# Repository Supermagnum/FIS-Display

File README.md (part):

# FIS-Display
VW Passat B6 FIS/MFA Display — Hardware Connections and Software Protocols.

## Table of contents

- [Disclaimer](#disclaimer)
- [What this project does](#what-this-project-does)
- [Gerber files and PCB manufacturing](#gerber-files-and-pcb-manufacturing)
- [Project structure](#project-structure)
- [1. System Overview](#1-system-overview)
- [2. Host Device — Navit with D-Bus](#2-host-device--navit-with-d-bus)
  - [2.1 Supported Platforms](#21-supported-platforms)
  - [2.2 D-Bus Service Details](#22-d-bus-service-details)
  - [2.3 Key Attributes to Subscribe To](#23-key-attributes-to-subscribe-to)
  - [2.4 Navigation Status Values](#24-navigation-status-values)
  - [2.5 D-Bus Listener to Pico Bridge Script](#25-d-bus-listener--pico-bridge-script)
- [3. Serial Protocol (Host to Pico, 115200 baud)](#3-serial-protocol-host--pico-115200-baud-newline-terminated-ascii)
  - [3.1 Eco mode icon (driver-break, D-Bus)](#31-eco-mode-icon-driver-break-d-bus)
- [4. Transport — USB CDC or Bluetooth SPP](#4-transport--usb-cdc-or-bluetooth-spp)
  - [USB CDC](#usb-cdc)
  - [Bluetooth SPP](#bluetooth-spp)
- [5. Hardware](#5-hardware)
  - [5.1 Controller — Raspberry Pi Pico 2 W](#51-controller--raspberry-pi-pico-2-w)
  - [5.2 The 3LB (Three-Line Bus)](#52-the-3lb-three-line-bus)
  - [5.3 Level Shifting](#53-level-shifting)
  - [5.4 Instrument Cluster Connector (Green T32a)](#54-instrument-cluster-connector-green-t32a)
  - [5.5 3LB connection: pigtails or wire-to-wire (Molex kit)](#55-3lb-connection-pigtails-or-wire-to-wire-molex-kit)
  - [5.6 Pico 2 W GPIO Pinout](#56-pico-2-w-gpio-pinout)
  - [5.7 Cluster Coding Prerequisite](#57-cluster-coding-prerequisite)
- [6. The 3LB Protocol](#6-the-3lb-protocol)
  - [6.1 Open Source Libraries (Reference)](#61-open-source-libraries-reference)
  - [6.2 Display](#62-display)
  - [6.3 OEM radio: CAN time and display (reference only)](#63-oem-radio-can-time-and-display-reference-only)
  - [6.4 Other potentially useful CAN messages (reference only)](#64-other-potentially-useful-can-messages-reference-only)
- [7. Firmware Runtime Behaviour](#7-firmware-runtime-behaviour)
- [8. Software Stack Summary](#8-software-stack-summary)
- [9. Key References](#9-key-references)
- [10. Possible screen upgrade](#10-possible-screen-upgrade)

---
## Disclaimer

> The creator takes no responsibility for damages, immobile car, injury, or any other loss arising from the use of this project, its firmware, PCB design, or documentation. Use at your own risk.

## What this project does

[Navit](https://github.com/navit-gps/navit) is an open-source, modular turn-by-turn navigation engine that can run on Linux, Android, and other platforms. This project uses Navit on a host device (with D-Bus enabled) to drive the car's FIS/MFA display.

This repository provides firmware, PCB design, and documentation to show Navit navigation (and optionally media, call, clock) on the VW Passat B6 (3C) FIS/MFA display. 

A host device runs Navit with D-Bus and sends a simple serial protocol to a Raspberry Pi Pico 2 W over USB or Bluetooth (pair once as FIS-Bridge). 
The Pico injects frames onto the car's 3LB bus during idle gaps so the cluster shows turn-by-turn directions, street name, distance, and maneuver icons; when not navigating, it can show media track info, incoming call caller ID, or a clock screen with GPS time, ETA (e.g. ARR 14:32), remaining distance, and compass heading. 

The firmware supports CAN bus (MCP2561 on GPIO 11/12, 100 kbit/s, software CAN 2.0A send/receive); it is disabled by default and can be enabled with CFG:CAN:1. The Pico is a middleman only; all navigation logic stays on the host. When CAN bus is enabled, it can adjust your clock automatically. 

A separate display-test firmware is provided for bench-testing the cluster without a Navit host.

PCB and schematic are designed in [KiCad](https://www.kicad.org/). Design files and Gerbers are in [pcb-files/](pcb-files/). See [Gerber files and PCB manufacturing](#gerber-files-and-pcb-manufacturing) for what they are and how to use them.

> **Note:** The firmware in `firmware/` is **experimental and untested on a real vehicle**. Validate on the bench before connecting to the car. See [firmware/README.md](firmware/README.md) for build and flash instructions; that file also explains how to install the Raspberry Pi Pico SDK if it is missing.

## Gerber files and PCB manufacturing

**What are Gerber files?** Gerber is the standard format used by PCB manufacturers to produce printed circuit boards. Each file describes one layer of the board (copper, solder mask, silkscreen, etc.) as vector graphics. The manufacturer combines these files to fabricate and assemble the PCB. This repository provides Gerbers exported from the KiCad project in [pcb-files/FIS-display/](pcb-files/FIS-display/).

**What is in this repo:** In [pcb-files/FIS-display/gerbers/](pcb-files/FIS-display/gerbers/) you will find:

- **Copper layers:** `F_Cu.gbr` (top copper), `B_Cu.gbr` (bottom copper)
- **Solder mask:** `F_Mask.gbr`, `B_Mask.gbr`
- **Silkscreen:** `F_Silkscreen.gbr`, `B_Silkscreen.gbr`
- **Solder paste (SMD stencil):** `F_Paste.gbr`, `B_Paste.gbr`
- **Board outline:** `Edge_Cuts.gbr`
- **Drill files:** `*.drl` (through-hole and non-plated drill data)

**How to use them:**

1. **Ordering PCBs:** Zip the contents of the `gerbers/` folder (all `.gbr` and `.drl` files, and the `.gbrjob` file if the manufacturer supports it) and upload the zip to a PCB fab (e.g. JLCPCB, PCBWay, OSH Park, or similar). Select the correct units (usually mm) and board thickness; the fab will use the Gerbers to produce the boards. Use the same BOM as in [firmware/BOM.md](firmware/BOM.md) for sourcing components.

2. **Viewing without KiCad:** You can inspect the layers with a Gerber viewer (e.g. [GerberView](https://www.gerber-viewer.com/), or the online viewer many fabs provide) to check traces, pads, and outline before ordering.

3. **Editing the design:** Open the KiCad project in [pcb-files/FIS-display/](pcb-files/FIS-display/) (`.kicad_pro`, `.kicad_sch`, `.kicad_pcb`) in [KiCad](https://www.kicad.org/). After any change, re-export Gerbers from KiCad (File → Plot, then generate drill files) and replace the files in `gerbers/` before ordering new boards.

---

## Project structure

This repository uses **no symlinks**; all paths are normal directories and files so that every system can clone and use it without symlink support.

| Item | Description |
|------|-------------|
| [firmware/](firmware/) | Main Pico 2 W firmware: 3LB RX/TX, serial protocol, nav/media/clock injection, graphics. |
| [firmware/README.md](firmware/README.md) | Build, flash, pinout, and firmware behaviour. |
| [firmware/BOM.md](firmware/BOM.md) | Bill of materials for the PCB. |
| [firmware-display-test/](firmware-display-test/) | Standalone display test firmware: cycles through all modes (nav text, icons, call, media, clock) every 4 seconds. |
| [firmware-display-test/README.md](firmware-display-test/README.md) | How to build and use the display test. |
| [nav-icons/](nav-icons/) | Navigation and status icon SVGs (sources for the bitmaps in `firmware/fis_nav_icons.h`). See [nav-icons/README.md](nav-icons/README.md) for adding new icons. |
| [tools/](tools/) | Build/convert helpers. [tools/svg_to_fis_icon.py](tools/svg_to_fis_icon.py) converts SVG to the 64x64 1-bit C array format. [tools/navit_dbus_to_pico_bridge.py](tools/navit_dbus_to_pico_bridge.py) runs on the host and forwards Navit D-Bus (including eco_mode_fuel_enabled) to the Pico over serial. |
| [PQ35_46_ACAN_KMatrix_V5.20.6F_20160530_MH.xlsx](PQ35_46_ACAN_KMatrix_V5.20.6F_20160530_MH.xlsx) | VW/Audi PQ35/46 CAN matrix (reference). |
| [PQ35_46_ACAN_Glossary_DE_EN.md](PQ35_46_ACAN_Glossary_DE_EN.md) | German–English translation table for the CAN matrix document. |
| [pcb-files/](pcb-files/) | PCB design (KiCad) and [Gerber files](pcb-files/FIS-display/gerbers/) for manufacturing. See [Gerber files and PCB manufacturing](#gerber-files-and-pcb-manufacturing). |

---

## 1. System Overview

```
┌──────────────────────────────────────────────────────────┐
│  Host device running Navit with D-Bus enabled            │
│                                                          │
│  Examples:                                               │
│  • Android head unit (Navit built with D-Bus support)    │
│  • Linux carputer / Raspberry Pi running Navit           │
│  • Any platform where libbinding_dbus.so is active       │
│                                                          │
│  D-Bus listener translates Navit signals to serial       │
│  protocol and forwards to Pico over USB or Bluetooth     │
└────────────┬─────────────────────────┬───────────────────┘
             │                         │
     USB CDC serial            Bluetooth SPP
     /dev/ttyACM0              (onboard CYW43439)
     (also powers Pico)        "FIS-Bridge" PIN 0000
             │                         │
             └──────────┬──────────────┘
                        │
               ┌────────▼─────────┐
               │ Raspberry Pi     │
               │ Pico 2 W         │
               │ (RP2350)         │
               │                  │
               │ Middleman:       │
               │ serial -> 3LB;   │
               │ optional: GPIO   │
               │ 11/12 -> MCP2561 │
               └────────┬─────────┘
                        │
         ┌──────────────┼──────────────┐
         │              │              │
         ▼              │              ▼
 3LB (ENA/CLK/DATA)     │      Optional CAN (if enabled):
 via BS170 level        │      GPIO 11 (TX), 12 (RX) ->
 shifters (3.3V<->5V)   │      MCP2561 (TXD/RXD) -> CAN-H/CAN-L
         │              │              │
         ▼              │              ▼
 ┌──────────────────┐   │   ┌──────────────────────────┐
 │ VW Passat B6 (3C) │   │   │ Komfort-CAN (K-CAN)      │
 │ FIS/MFA cluster   │◄──┘   │ 100 kbit/s (when fitted) │
 │ 64x88 px, 1-bit   │       └──────────────────────────┘
 └────────┬──────────┘
          │
          ▼
 ┌───────────────────────┐
 │ Original ECU          │
 │ (talks 3LB natively,  │
 │  Pico co-exists via   │
 │  ENA arbitration)     │
 └───────────────────────┘
```

The Pico 2 W is a **pure middleman**. It has no navigation intelligence — it only receives
the serial protocol from the host device and injects the translated frames onto the 3LB bus.

All navigation logic stays on the host device running Navit. Optionally, when CAN is enabled
(see [5.6 Pico 2 W GPIO Pinout](#56-pico-2-w-gpio-pinout)), the Pico can communicate with the
vehicle Komfort-CAN (Comfort CAN / K-CAN, 100 kbit/s) via GPIO 11/12 to the MCP2561 (TXD/RXD only).

The original ECU continues to talk to the FIS/MFA natively over 3LB at all times. The Pico co-exists on the bus using the ENA line for arbitration — no relay or analog switch is needed.

> **Note:** The OEM radio has been replaced with an aftermarket head unit. The head unit does
> **not** communicate over 3LB. Only the original ECU talks to the FIS/MFA natively over 3LB.

---

## 2. Host Device — Navit with D-Bus

### 2.1 Supported Platforms

Navit can be built with D-Bus support (`libbinding_dbus.so`) on multiple platforms:

| Platform | Notes |
|----------|-------|
| Android head unit | Navit built with D-Bus support. Android includes D-Bus (`android_external_dbus`) |
| Linux carputer | Native D-Bus session bus, full support |
| Raspberry Pi (Linux) | Native D-Bus session bus, full support |
| Any Linux-based system | Native D-Bus session bus, full support |

Enable D-Bus in `navit.xml`:
```xml
<plugin path="$NAVIT_LIBDIR/*/${NAVIT_LIBPREFIX}libbinding_dbus.so" active="yes"/>
```

### 2.2 D-Bus Service Details

| Item | Value |
|------|-------|
| Service name | `org.navit_project.navit` |
| Bus type | Session bus |
| Main object | `/org/navit_project/navit/default_navit` |
| Route object | `/org/navit_project/navit/default_navit/default_route` |
| Vehicle object | `/org/navit_project/navit/default_navit/default_vehicle` |

### 2.3 Key Attributes to Subscribe To

| Attribute | Meaning |
|-----------|---------|
| `navigation_next_turn` | Upcoming maneuver type |
| `navigation_distance_turn` | Metres to next turn |
| `navigation_street_name` | Next street name |
| `navigation_street_name_systematic` | Route number |
| `navigation_status` | Routing state |
| `position_speed` | Current speed |
| `eta` | Estimated arrival (Unix timestamp); sent as `NAV:ETA`, shown in local time on FIS clock line |
| `destination_length` | Remaining distance to destination (m); sent as `NAV:REMAIN`, shown on FIS clock line |
| `position_direction` | Heading in degrees (0-360); sent as `NAV:HEAD`, shown as compass (N, NE, E, ...) on FIS |
| `position_time_iso8601` | GPS time UTC, format `YYYY-MM-DDTHH:MM:SSZ` (for FIS clock) |
| `position_coord_geo` | GPS latitude/longitude (for timezone lookup; vehicle attribute) |

### 2.4 Navigation Status Values

| Value | Meaning |
|-------|---------|
| `no_route` | No active route |
| `no_destination` | No destination set |
| `position_wait` | Waiting for GPS |
| `calculating` | Initial calculation |
| `recalculating` | Rerouting |
| `routing` | Active guidance |

### 2.5 D-Bus Listener to Pico Bridge Script

A bridge script runs on the host device and forwards Navit D-Bus attributes to the Pico over USB CDC or Bluetooth SPP. This repo includes **`tools/navit_dbus_to_pico_bridge.py`**, which implements the protocol and **eco_mode_fuel_enabled** support (Driver Break plugin): when `get_attr("eco_mode_fuel_enabled")` is true and a route has just been calculated (`navigation_status` = `routing`), it sends the eco icon for a short period (default 2.5 s), then the real first turn and distance so the FIS never shows eco instead of routing.

The driver-break plugin is awaiting merge and hardware testing; see [navit-gps/navit#1419](https://github.com/navit-gps/navit/pull/1419).

**Run (host):**
```bash
python3 tools/navit_dbus_to_pico_bridge.py --port /dev/ttyACM0   # USB CDC
python3 tools/navit_dbus_to_pico_bridge.py --port /dev/rfcomm0 --eco-seconds 2.5   # Bluetooth SPP
```

**Requirements:** Python 3, `pyserial`, PyGObject (`gi.repository.GLib`), `dbus`. Optional: Driver Break plugin in Navit for `eco_mode_fuel_enabled` (OBD-II / J1939 / MegaSquirt or adaptive fuel learning).

**Inline example (minimal, no eco logic)** for reference:

```python
#!/usr/bin/env python3
"""
Navit D-Bus listener -> Pico 2 W serial bridge.
Runs on any platform where Navit is built with libbinding_dbus.so active:
Android (with D-Bus support), Linux carputer, Raspberry Pi, etc.
Transport: USB CDC or Bluetooth SPP -- configure SERIAL_PORT below.
"""

import serial
import dbus
import dbus.mainloop.glib
from gi.repository import GLib

SERIAL_PORT = "/dev/ttyACM0"   # USB CDC, or e.g. /dev/rfcomm0 for Bluetooth SPP
BAUD = 115200

WATCHED = [
    "navigation_next_turn",
    "navigation_distance_turn",
    "navigation_street_name",
    "navigation_status",
    "eta",
    "destination_length",      # remaining distance (m) -> NAV:REMAIN, shown on FIS clock line
    "position_direction",      # heading 0-360 -> NAV:HEAD, shown as compass (N, NE, E, ...)
    "position_time_iso8601",   # UTC GPS time for FIS clock (format YYYY-MM-DDTHH:MM:SSZ)
    "position_coord_geo",      # lat/lon for timezone lookup (vehicle attribute)
]

MANEUVER_MAP = {
    "straight":          "straight",
    "turn_left":         "turn_left",
    "turn_right":        "turn_right",
    "turn_slight_left":  "slight_left",
    "turn_slight_right": "slight_right",
    "turn_sharp_left":   "sharp_left",
    "turn_sharp_right":  "sharp_right",
    "u_turn":            "u_turn",
    "keep_left":         "keep_left",
    "keep_right":        "keep_right",
    "destination":       "destination",
}

class NavitBridge:
    def __init__(self):
        self.ser = serial.Serial(SERIAL_PORT, BAUD, timeout=1)
        dbus.mainloop.glib.DBusGMainLoop(set_as_default=True)
        bus = dbus.SessionBus()
        obj = bus.get_object("org.navit_project.navit",
                             "/org/navit_project/navit/default_navit")
        iface = dbus.Interface(obj, dbus_interface="org.navit_project.navit")
        cb_path = iface.callback_attr_new()
        for attr in WATCHED:
            iface.add_attr(cb_path, attr)
        bus.add_signal_receiver(
            self.on_update,
            signal_name="callback_attr_update",
            dbus_interface="org.navit_project.navit",
            path=cb_path,
        )

    def on_update(self, attr_name, value):
        msg = None
        if attr_name == "navigation_next_turn":
            code = MANEUVER_MAP.get(str(value), str(value))
            msg = f"NAV:TURN:{code}\n"
        elif attr_name == "navigation_distance_turn":
            msg = f"NAV:DIST:{int(value)}\n"
        elif attr_name == "navigation_street_name":
            msg = f"NAV:STREET:{str(value)[:20]}\n"
        elif attr_name == "navigation_status":
            msg = f"NAV:STATUS:{str(value)}\n"
        elif attr_name == "eta":
            msg = f"NAV:ETA:{int(value)}\n"
        elif attr_name == "destination_length":
            msg = f"NAV:REMAIN:{int(value)}\n"
        elif attr_name == "position_direction":
            msg = f"NAV:HEAD:{int(value)}\n"
        elif attr_name == "position_time_iso8601":
            msg = f"NAV:TIME:{str(value)}\n"
        elif attr_name == "position_coord_geo":
            # value is typically (lng, lat) or struct; adapt to your D-Bus binding
            try:
                lat, lon = float(value[1]), float(value[0])  # (lng, lat) from Navit
                msg = f"NAV:POS:{lat:.4f},{lon:.4f}\n"
            except (IndexError, TypeError, ValueError):
                pass
        if msg:
            self.ser.write(msg.encode())

    def run(self):
        GLib.MainLoop().run()

if __name__ == "__main__":
    NavitBridge().run()
```

For full behaviour including eco icon when `eco_mode_fuel_enabled` is true, use **`tools/navit_dbus_to_pico_bridge.py`** (see above).

---

## 3. Serial Protocol (Host → Pico, 115200 baud, newline-terminated ASCII)

The same protocol is used regardless of whether the transport is USB CDC or Bluetooth SPP.

| Message | Meaning |
|---------|---------|
| `NAV:TURN:<code>` | Upcoming maneuver type. For eco icon (driver-break) see [3.1 Eco mode icon](#31-eco-mode-icon-driver-break-d-bus): use `eco_mode` or `eco` only when `eco_mode_fuel_enabled` is true and route is ready (see 3.1); it must **not** override routing instructions. |
| `NAV:DIST:<metres>` | Distance to next turn |
| `NAV:STREET:<n>` | Next street name (max 20 chars) |
| `NAV:STATUS:<status>` | Navit routing status |
| `NAV:ETA:<unix_ts>` | Estimated arrival (Unix timestamp); converted to local time and shown on clock line 2 as e.g. ARR14:32 |
| `NAV:REMAIN:<metres>` | Remaining distance to destination (from Navit `destination_length`); shown on clock line |
| `NAV:HEAD:<degrees>` | Heading 0-360 (from Navit `position_direction`); shown as compass on clock line |
| `NAV:TIME:<iso8601>` | GPS time UTC, e.g. `2026-03-14T12:34:56Z` (from Navit `position_time_iso8601`) |
| `NAV:POS:<lat>,<lon>` | GPS position in decimal degrees (from Navit `position_coord_geo`), e.g. `59.91,10.75` |
| `BT:TRACK:<info>` | Media track info from head unit |
| `BT:CALL:<caller>` | Incoming call caller ID |
| `BT:CALLEND` | Call ended |

### 3.1 Eco mode icon (driver-break, D-Bus)

The **eco mode** icon on the FIS is intended for the [Driver Break plugin](https://github.com/Supermagnum/navit/blob/feature/driver-break/docs/user/plugins/driver-break/index.rst) when fuel/energy is used in routing (ECU or adaptive fuel data). It must **never override routing instructions**: the host must only show the eco icon when appropriate and only for a short moment (e.g. after route planning finishes, before the first maneuver is displayed).

**Driver-break D-Bus attribute: `eco_mode_fuel_enabled`**

The plugin exposes a boolean attribute **eco_mode_fuel_enabled** on the Navit D-Bus interface. It is **true** when either (1) an ECU backend is available and running (OBD-II, J1939, or MegaSquirt), or (2) adaptive fuel learning is enabled in the plugin configuration. When **false**, no live ECU data and no adaptive learning are in use (energy-based routing may still be available without fuel data). See the [Driver Break D-Bus API (eco_mode_fuel_enabled)](https://github.com/Supermagnum/navit/blob/feature/driver-break/docs/user/plugins/driver-break/dbus.rst) for service, object path, interface, and examples in Python and `dbus-send`.

- **Service:** `org.navit_project.navit`
- **Method:** `get_attr("eco_mode_fuel_enabled")` on the navit object; returns `(attrname, value)` with a D-Bus boolean.

**When to show the eco icon**

- **`eco_mode_fuel_enabled` is true** (ECU running or adaptive fuel learning enabled).
- **Navit has planned or finished planning** a route that uses energy-based routing (fuel cost in the cost function).
- **Do not show eco when there is an active maneuver to display.** Example flow: when Navit finishes calculating a route and the above conditions are true, show the eco icon for a short period (e.g. 2–3 seconds), then send the actual first turn (`navigation_next_turn`) and distance so the FIS switches to normal turn-by-turn. The eco icon is an informational "route was planned with eco/fuel" hint, not a substitute for maneuver icons.

**Bridge script logic**

1. **Read the attribute** (e.g. on a timer or when `navigation_status` changes): call `get_attr("eco_mode_fuel_enabled")` on the navit object (see [dbus.rst](https://github.com/Supermagnum/navit/blob/feature/driver-break/docs/user/plugins/driver-break/dbus.rst) for object path and Python/dbus-send examples).
2. **Policy:** Send `NAV:TURN:eco_mode` to the Pico only when:
   - `eco_mode_fuel_enabled` is true, and
   - Route planning has just completed (e.g. `navigation_status` went to `routing`) or the route is ready and you are about to send the first maneuver.
3. Send `NAV:TURN:eco_mode` for a **short fixed duration** (e.g. 2–3 seconds), then immediately send the real first turn and distance (`NAV:TURN:<code>`, `NAV:DIST:<m>`) so the FIS shows the actual routing instruction. Never send or keep sending `eco_mode` when the user should see a turn icon (left, right, etc.).

The driver-break plugin is awaiting merge into the official Navit repo and hardware testing. See: https://github.com/navit-gps/navit/pull/1419

**Firmware behaviour:** The Pico displays whatever `NAV:TURN` code the host last sent. The **host is responsible** for never letting eco_mode override a maneuver: the bridge must only send `NAV:TURN:eco_mode` in the narrow window described above and then replace it with the real maneuver.

**Summary:** Eco icon = show only when `eco_mode_fuel_enabled` is true and route planning has just finished; display it briefly, then always switch to the real first (and subsequent) routing instructions.

**Feature toggles (clock screen):** Send `CFG:<name>:0` or `CFG:<name>:1` to enable or disable what is shown. Clock/ETA/compass/remain default to 1 (on). CAN bus has **full firmware support** (send/receive, 100 kbit/s, MCP2561) but is **disabled by default** (0).

| Message | Effect |
|---------|--------|
| `CFG:CLOCK:0` / `CFG:CLOCK:1` | Clock (time from GPS, set automatically); 0 = do not show clock on FIS |
| `CFG:ETA:0` / `CFG:ETA:1` | ETA in local time on clock line 2 (e.g. ARR14:32) |
| `CFG:COMPASS:0` / `CFG:COMPASS:1` | Compass heading (N, NE, ...) on clock line 2 |
| `CFG:REMAIN:0` / `CFG:REMAIN:1` | Remaining distance on clock line 2 |
| `CFG:CAN:0` / `CFG:CAN:1` | CAN bus (full support: send/receive at 100 kbit/s, **disabled by default**). Enable with 1 when MCP2561 is connected to GPIO 11/12. |

---

## 4. Transport — USB CDC or Bluetooth SPP

The host device can connect to the Pico over either transport. The Pico listens on both
USB CDC and Bluetooth SPP simultaneously.

### USB CDC
- Connect a USB cable from the host to the Pico USB port
- Pico appears as `/dev/ttyACM0` (Linux) or equivalent on Android
- **Also provides 5 V power to the Pico via VSYS** — no separate power supply needed
- Baud rate: 115200

### Bluetooth SPP
- Pico advertises as `FIS-Bridge` using classic Bluetooth SPP via BTstack (onboard CYW43439)
- No external Bluetooth module required
- **Pair once:** scan for `FIS-Bridge`, enter PIN `0000` if prompted — reconnects automatically
- On Linux: Pico appears as `/dev/rfcomm0` after pairing
- Baud rate: 115200

> If using Bluetooth only (no USB), the Pico needs a separate 5 V power source via the VSYS
> pin — e.g. a car USB adapter or a 12 V → 5 V regulator on the PCB.

---

## 5. Hardware

### 5.1 Controller — Raspberry Pi Pico 2 W

| Property | Value |
|----------|-------|
| MCU | RP2350 (dual-core Cortex-M33, 150 MHz) |
| RAM | 520 KB SRAM |
| Flash | 4 MB |
| Wireless | Infineon CYW43439 — WiFi + classic Bluetooth |
| Logic level | 3.3 V GPIO |
| Power | 5 V via VSYS (USB or external) |
| DigiKey P/N | SC0919 |

### 5.2 The 3LB (Three-Line Bus)

| Wire | Function | Direction |
|------|----------|-----------|
| ENA | Enable / bus arbitration | Bidirectional |
| DATA | Serial data | Master → Cluster |
| CLK | Clock | Master → Cluster |

Bus runs at **5 V logic**. The 3LB clock speed is **suspected to be ~125–130 kHz** (transmission/bit rate). The actual documented value is difficult to find; the BAP FCNav function catalogue does not specify the physical layer, and other sources sometimes quote conflicting numbers (e.g. 2300 Hz or 2300 kHz). The firmware is configured for ~125 kHz by default; see below for how to measure the speed on your bus and adjust the code. Pico GPIO is 3.3 V — level shifting required on all lines.

**Bus arbitration:** Before transmitting, a master pulls ENA low to claim the bus. If ENA is already
low (another device is transmitting), it waits. The cluster acknowledges with a 100 µs pulse (e.g. ENA high). The Pico and ECU safely share the bus without any relay or switch.

**Measuring 3LB clock speed and adjusting the firmware:** To confirm or correct the bus speed on your cluster:

1. **Measure the CLK line** with an oscilloscope or logic analyzer while the OEM radio or nav unit is transmitting to the cluster (or while the Pico is transmitting). Measure the frequency of the CLK signal during an active frame (ENA low). One full clock period = one bit; the frequency in Hz is the bit rate.
2. **If your measured frequency differs from ~125 kHz**, edit the firmware to match. In `firmware/fis_display.c`, change the constant `FIS_3LB_TX_CLK_HZ` (default 125000) to your measured value in Hz. Rebuild and flash. Example: if you measure 130 kHz, set `#define FIS_3LB_TX_CLK_HZ 130000u`.
3. **Optional:** If you have a different PIO program with a different number of cycles per bit, adjust `FIS_3LB_TX_CYCLES_PER_BIT` (default 6) to match so the divider calculation stays correct.

### 5.3 Level Shifting

6× **BS170** N-channel MOSFET (TO-92, through-hole), one per 3LB GPIO line (3 RX + 3 TX).
Each channel uses two 2.2 kΩ pull-up resistors — one to 3.3 V, one to 5 V. Use non-inductive resistors (e.g. metal film or SMD thick/thin film); avoid wirewound types.

| Part | DigiKey P/N | Qty |
|------|-------------|-----|
| BS170 MOSFET TO-92 THT | BS170-ND | 6 |
| 2.2 kΩ resistor 0.25 W THT (non-inductive) | — | 12 |

BS170 pinout (flat face toward you, left to right): **Source — Gate — Drain**.

### 5.4 Instrument Cluster Connector (Green T32a)

| T32a Pin | Signal |
|----------|--------|
| 30 | DATA |
| 31 | CLK |
| 32 | ENA |

Connector type: Kostal MLK 1.2 / MQS 0.63 mm. Use a VAG pin tool to back-probe terminals.
Do not cut harness wires unless you are absolutely sure what you are doing.
One option is to cut the harness wires needed and add connectors so you can plug the PCB in line; then you can unplug both sides and connect them directly to bypass the board for repairs or to restore original function. Use the Molex 3-circuit kit (see below) for pigtails from the PCB or for a pure wire-to-wire connection.

### 5.5 3LB connection: pigtails or wire-to-wire (Molex kit)

No PCB-mounted connector. Use one **Molex 3-circuit connector kit** (DigiKey **23-0766500064-ND**, Molex **0766500064**, "KIT CONN STD .062" 3 CIRCUITS"). The kit is the complete solution for both PCB pigtails and wire-to-wire.

**With PCB (pigtails):** Solder two short pigtail wires directly to the PCB RX and TX pad areas. On the free end of each pigtail, crimp the correct connector from the kit:

| Side | PCB pad | Free end (from kit) |
|------|---------|---------------------|
| **RX** | Solder wire to PCB RX pads | Female receptacle housing **0003061038** with socket terminals **0002061103** |
| **TX** | Solder wire to PCB TX pads | Plug housing **0003062033** with pin terminals **0002062103** |

Incoming field cables then plug into those pigtails — female into male, male into female. The different housing genders prevent swapping RX and TX.

**Wire-to-wire (no PCB):** To connect two cables with no board in between, plug the kit female receptacle housing directly into the male plug housing. No PCB, no soldering, no extra parts.

| Part | DigiKey P/N | Qty |
|------|-------------|-----|
| Molex 3-circuit connector kit (.062" / 1.57 mm) | 23-0766500064-ND | 1 |

### 5.6 Pico 2 W GPIO Pinout

**3LB RX — monitor ECU frames, detect bus idle (inputs, via level shifter):**

| GPIO | Signal |
|------|--------|
| GPIO0 | FIS_PIN_ENA — monitors bus idle state |
| GPIO1 | FIS_PIN_CLK — input to PIO SM0 |
| GPIO2 | FIS_PIN_DATA — input to PIO SM0 |

**3LB TX — inject frames during idle gaps (outputs, via level shifter):**

| GPIO | Signal |
|------|--------|
| GPIO3 | FIS_PIN_ENA_OUT — claims bus before injecting |
| GPIO4 | FIS_PIN_CLK_OUT — PIO SM1 side-set |
| GPIO5 | FIS_PIN_DATA_OUT — PIO SM1 out_base |

**Optional CAN (firmware supports full CAN; when enabled, MCP2561):** On the VW Passat B6 (PQ46 platform) the bus connecting the instrument cluster to the rest of the modules is the **Komfort-CAN** (Comfort CAN), also referred to as **K-CAN** or **KCAN**. The CAN transceiver used is the MCP2561. It has only 2 signal connections: TXD and RXD. 3.3 V logic; no level shifter needed. See `firmware/fis_can.h` and firmware README.

| GPIO   | Signal         | Direction | Notes                    |
|--------|----------------|-----------|---------------------------|
| GPIO11 | FIS_CAN_PIN_TX | Out       | TX CAN to MCP2561 TXD     |
| GPIO12 | FIS_CAN_PIN_RX | In        | RX CAN from MCP2561 RXD   |

MCP2561 CANH/CANL connect to the vehicle Komfort-CAN (Comfort CAN / K-CAN, 100 kbit/s). For when to add a 120 ohm termination (tapped in middle vs replacing radio vs bench), see firmware README.

**PQ46 CAN buses:** The Komfort-CAN is distinct from the other two CAN buses on the platform:

| Bus | Bit rate | Typical traffic |
|-----|----------|------------------|
| **Komfort-CAN** (K-CAN) | 100 kbit/s | Instrument cluster, convenience modules, gateway; messages like mKombi_1, mDiagnose_1 |
| **Antriebs-CAN** (ACAN / Drivetrain CAN) | 500 kbit/s | Engine, ABS, airbag, gearbox |
| **Infotainment-CAN** (ICAN) | 100 kbit/s | Radio, navigation, phone module |

The **CAN gateway (J533)** sits between these buses and bridges messages as needed. When your Pico (via MCP2561) taps into the bus to read or send messages such as mKombi_1, mDiagnose_1, etc., it is connecting to the **Komfort-CAN** (K-CAN), not to ACAN or ICAN.

### 5.7 Cluster Coding Prerequisite

Code the cluster using **VCDS** or **OBDeleven**, Module **17 — Instruments**:
enable **"Navigation present"**. Without this the navigation slot in the FIS/MFA is inactive
even if the Pico sends correct 3LB frames.

---

## 6. The 3LB Protocol

### 6.1 Open Source Libraries (Reference)

| Library | URL | Notes |
|---------|-----|-------|
| TLBFISLib | https://github.com/domnulvlad/TLBFISLib | Most complete, actively maintained |
| VAGFISWriter | https://github.com/tomaskovacik/VAGFISWriter | Original reverse-engineered implementation |
| FISCuntrol | https://github.com/adamforbes92/FISCuntrol | Complete project, author uses in own car |
| FISBlocks | https://github.com/ibanezgomez/FISBlocks | 3LB + KWP1281 OBD combined |

The Pico firmware reimplements 3LB directly in PIO state machines timed to the BAP FCNav
SDP30DF48V280F specification — no Arduino library dependency.

### 6.2 Display

The FIS/MFA (Fahrerinformationssystem / Multifunktionsanzeige) screen is a **64×88 pixel
monochrome LCD**, 1-bit. Navigation maneuver icons are pre-generated 64×64 px 1-bit arrays
stored in flash (`firmware/fis_nav_icons.h`) and rendered with:
```c
GraphicFromArray(x, y, width, height, array, 0); // 0 = flash/PROGMEM
```

### 6.3 OEM radio: CAN time and display (reference only)

The **original VW radio** set the instrument cluster time via the **CAN bus** (CAN-H / CAN-L), using time it received from the **FM RDS network**. This project does **not** use CAN for the clock; the Pico sets the FIS clock from GPS (Navit) over serial and 3LB only. The following is documented for reference.

**OEM messages implemented:** When CAN is enabled (`CFG:CAN:1`), the firmware sends **mDiagnose_1** (0x7D0) with local date/time derived from GPS (NAV:TIME + position for timezone) every 1000 ms, and **mEinheiten** (0x60E) with display format (24 h, EU date, units). The cluster can use mDiagnose_1 to set its internal clock. The FIS clock display is still driven by the serial protocol and 3LB injection; mDiagnose_1 allows the cluster’s own time display to stay in sync when CAN is connected.

| Message | CAN ID | Length | Period | Description |
|---------|--------|--------|--------|-------------|
| **mDiagnose_1** | 0x7D0 (2000) | 8 bytes | 1000 ms | Date and time from radio (e.g. RDS). |
| **mEinheiten** | 0x60E (1550) | 2 bytes | 1000 ms | Display format flags (date/clock on-off, day of week). |

**mDiagnose_1 (0x7D0) — date and time**

| Signal | Byte | Start bit | Length | Range | Unit |
|--------|------|------------|--------|-------|------|
| DI1_Jahr (Year) | 4 | 4 | 7 bits | 0–127 → 2000–2127 | Year |
| DI1_Monat (Month) | 5 | 3 | 4 bits | 1–12 | Month |
| DI1_Tag (Day) | 5 | 7 | 5 bits | 0–31 | Day |
| DI1_Stunde (Hour) | 6 | 4 | 5 bits | 0–23 | Hours |
| DI1_Minute (Minute) | 7 | 1 | 6 bits | 0–59 | Minutes |
| DI1_Sekunde (Second) | 7 | 7 | 6 bits | 0–59 | Seconds |
| DI1_Zeit_alt (time stale) | 8 | 7 | 1 bit | — | 1 = time old/stale |

Sent cyclically every 1000 ms.

**mEinheiten (0x60E) — display format**

| Signal | Byte | Bit(s) | Description |
|--------|------|--------|-------------|
| EH1_Datum_Anzeige | 1 | 6 | Date display on/off |
| EH1_Uhr_Anzeige | 1 | 7 | Clock display on/off |
| EH1_Wochentag | 2 | 4–6 | Day of week |

Sent cyclically every 1000 ms.

### 6.4 Other potentially useful CAN messages (reference only)

**mDiagnose_1** and **mEinheiten** are implemented and sent when CAN is enabled (see 6.3). The following CAN frames are not yet implemented; they are documented for reference. You can add handling for these or other IDs using `fis_can_send()` / `fis_can_receive()`.

**Useful for FIS/display**

- **mKombi_1 (0x320)** — sent by the cluster, 10 ms cyclic: KO1_kmh (vehicle speed, bytes 4–5, 15 bits), KO1_angez_kmh (displayed speed including offset, bytes 6–7), KO1_Tankinhalt (fuel level), KO1_Warn_Tank (low fuel, 7 L), KO1_Oeldruck (oil pressure warning), KO1_Kuehlmittel (coolant warning), KO1_Vorgluehen (glow plug, diesel).
- **mKombi_2 (0x420)** — from cluster, 200 ms cyclic: KO2_gef_Auss_T / KO2_Aussen_T (outside temperature), KO2_Bel_Displ (display brightness %, for dimming FIS at night), KO2_Fehlereintr (fault stored).
- **mEinheiten (0x60E)** — units: EH1_Uhr_Anzeige (12h/24h), EH1_Datum_Anzeige (EU/US date), EH1_Wochentag (day of week 1=Mon…7=Sun), EH1_Einh_Temp (°C/°F), EH1_Einh_Strck (km/miles).

**Situational awareness**

- **mGate_Komf_1 (0x390)**, 100 ms: GK1_Rueckfahr (reverse), GK1_Warnblk_Status (hazards), GK1_Bremslicht, GK1_Abblendlicht / GK1_Fernlicht (headlights/high beam), GK1_Wischer_vorn (wipers), GK1_SH_laeuft (aux heater), door status (driver, passenger, rear L/R).
- **mZAS_1 (0x572)** — ignition: ZA1_Klemme_15 (ignition on), ZA1_Klemme_50 (starter), ZA1_S_Kontakt (key in).
- **mClima_1 (0x5E0)** — CL1_Kompressor (A/C on), CL1_Hecksch / CL1_Frontsch (rear/front screen heat), CL1_Restwaerme (residual heat).

**Parking (if equipped)**

- **Parkhilfe_01 (0x497)** — PDC: obstacle front/rear, beeper active, audio ducking request, system state.

**Other**

- **mKombi_3 (0x520)** — KO3_Kilometer (odometer), KO3_Standzeit (parked duration).
- **mSysteminfo_1 (0x5D0)** — SY1_Fzg_Derivat (body style), SY1_Notbrems_Status (emergency braking).

**Signal reference tables**

*mKombi_1 — 0x320 (from cluster, 10 ms cyclic)*

| Signal | Byte | Start bit | Len | Raw range | Physical | Unit | Scale |
|--------|------|-----------|-----|-----------|----------|------|-------|
| KO1_kmh | 4 | 1 | 15 | 0–32600 | 0–326 | km/h | 0.01 |
| KO1_angez_kmh | 6 | 6 | 10 | 0–1018 | 0–325.76 | km/h | 0.32 |
| KO1_Tankinhalt | 3 | 0 | 7 | 0–126 | 0–126 | litres | 1 |
| KO1_Warn_Tank | 1 | 6 | 1 | — | 1 = warning (7 L) | — | — |
| KO1_Oeldruck | 1 | 2 | 1 | — | 1 = low pressure | — | — |
| KO1_Kuehlmittel | 1 | 4 | 1 | — | 1 = coolant low | — | — |
| KO1_Vorgluehen | 1 | 7 | 1 | — | 1 = glow plug on | — | — |

KO1_angez_kmh spans bytes 6–7 (10 bits from bit 6); KO1_kmh spans bytes 4–5 (15 bits from bit 1). Little-endian.

*mKombi_2 — 0x420 (from cluster, 200 ms cyclic)*

| Signal | Byte | Start bit | Len | Raw range | Physical | Unit | Offset | Scale |
|--------|------|-----------|-----|-----------|----------|------|--------|-------|
| KO2_gef_Auss_T | 2 | 0 | 8 | 0–254 | −50 to +77 | °C | −50 | 0.5 |
| KO2_Aussen_T | 3 | 0 | 8 | 0–254 | −50 to +77 | °C | −50 | 0.5 |
| KO2_Bel_Displ | 6 | 0 | 7 | 0–100 | 0–100 | % | 0 | 1 |
| KO2_Fehlereintr | 1 | 7 | 1 | — | 1 = fault stored | — | — | — |

Temperature: °C = (raw × 0.5) − 50. Raw 0xFF = invalid.

*mEinheiten — 0x60E (1000 ms cyclic)*

| Signal | Byte | Start bit | Len | Values |
|--------|------|-----------|-----|--------|
| EH1_Uhr_Anzeige | 1 | 7 | 1 | 0 = 24 h, 1 = 12 h |
| EH1_Datum_Anzeige | 1 | 6 | 1 | 0 = EU (DD.MM), 1 = US (MM/DD) |
| EH1_Wochentag | 2 | 4 | 3 | 0 = init, 1 = Mon … 7 = Sun |
| EH1_Einh_Temp | 1 | 1 | 1 | 0 = °C, 1 = °F |
| EH1_Einh_Strck | 1 | 0 | 1 | 0 = km, 1 = miles |

*mGate_Komf_1 — 0x390 (100 ms cyclic)*

| Signal | Byte | Start bit | Len | Notes |
|--------|------|-----------|-----|-------|
| GK1_Rueckfahr | 4 | 4 | 1 | 1 = reverse |
| GK1_Warnblk_Status | 7 | 7 | 1 | 1 = hazards on |
| GK1_Bremslicht | 8 | 3 | 1 | 1 = brake light on |
| GK1_Abblendlicht | 7 | 0 | 1 | 1 = dipped beam |
| GK1_Fernlicht | 7 | 1 | 1 | 1 = high beam |
| GK1_Wischer_vorn | 7 | 2 | 1 | 1 = wipers moving |
| GK1_SH_laeuft | 8 | 0 | 1 | 1 = aux heater on |
| GK1_Fa_Tuerkont | 3 | 0 | 1 | Driver door |
| BSK_BT_geoeffnet | 6 | 1 | 1 | Passenger door |
| BSK_HL_geoeffnet | 4 | 2 | 1 | Rear left door |
| BSK_HR_geoeffnet | 4 | 3 | 1 | Rear right door |

*mZAS_1 — 0x572 (ignition/key)*

| Signal | Byte | Start bit | Len | Notes |
|--------|------|-----------|-----|-------|
| ZA1_S_Kontakt | 1 | 0 | 1 | 1 = key inserted |
| ZA1_Klemme_15 | 1 | 1 | 1 | 1 = ignition on |
| ZA1_Klemme_50 | 1 | 3 | 1 | 1 = starter engaged |

*mClima_1 — 0x5E0*

| Signal | Byte | Start bit | Len | Notes |
|--------|------|-----------|-----|-------|
| CL1_Kompressor | 1 | 4 | 1 | 1 = A/C on |
| CL1_Hecksch | 1 | 2 | 1 | 1 = rear screen heat |
| CL1_Frontsch | 1 | 3 | 1 | 1 = front screen heat |
| CL1_Restwaerme | 7 | 3 | 1 | 1 = residual heat on |

*Parkhilfe_01 — 0x497 (if equipped)*

| Signal | Byte | Start bit | Len | Notes |
|--------|------|-----------|-----|-------|
| PH_Opt_Anz_V_Hindernis | 3 | 2 | 1 | 1 = obstacle front |
| PH_Opt_Anz_H_Hindernis | 3 | 3 | 1 | 1 = obstacle rear |
| PH_Tongeber_V_aktiv | 3 | 4 | 1 | 1 = PDC beep front |
| PH_Tongeber_H_aktiv | 3 | 5 | 1 | 1 = PDC beep rear |
| PH_Anf_Audioabsenkung | 3 | 7 | 1 | 1 = audio duck request |
| PH_Systemzustand | 8 | 2 | 3 | 0 = off, 1 = reverse, 2 = front, 3 = both, 7 = fault |

*mKombi_3 — 0x520*

| Signal | Byte | Start bit | Len | Raw range | Physical | Unit | Scale |
|--------|------|-----------|-----|-----------|----------|------|-------|
| KO3_Kilometer | 6 | 0 | 20 | 0–1048575 | 0–1048575 | km | 1 |
| KO3_Standzeit | 4 | 0 | 15 | 0–32767 | 0–131068 | seconds | ×4 |

KO3_Standzeit = time since last ignition-off in 4-second steps (max ~36.4 h).

*mSysteminfo_1 — 0x5D0*

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
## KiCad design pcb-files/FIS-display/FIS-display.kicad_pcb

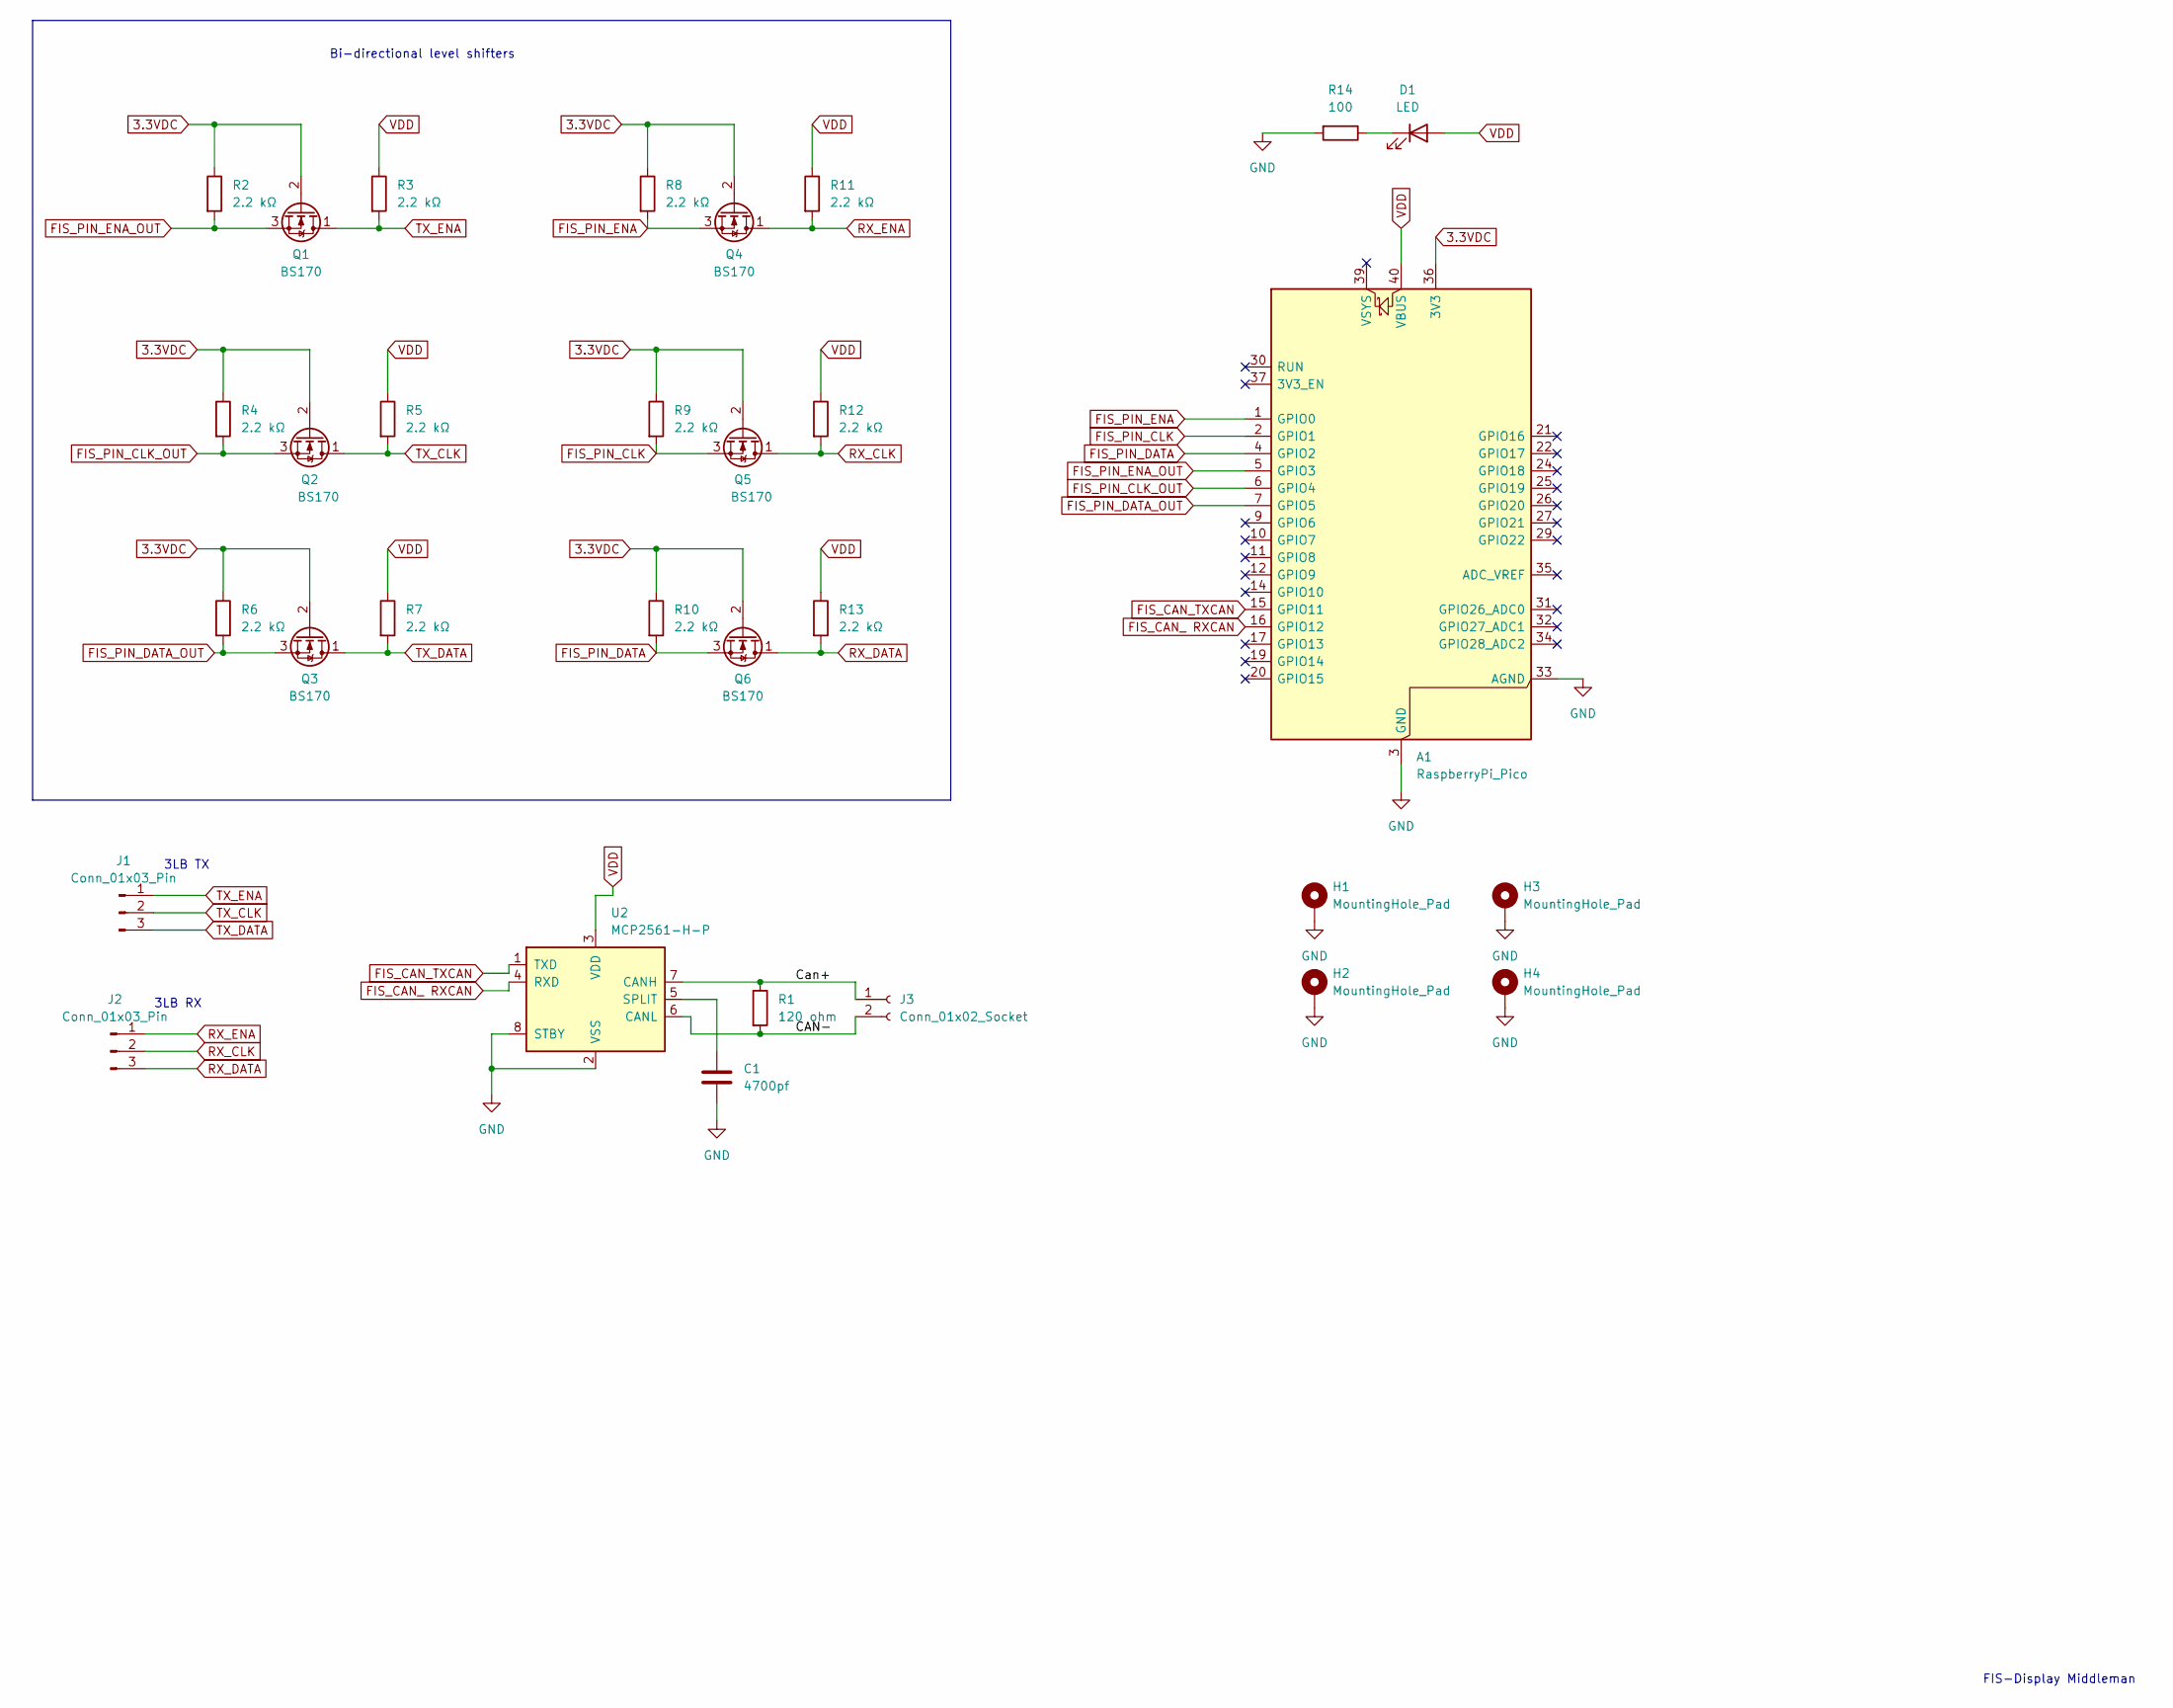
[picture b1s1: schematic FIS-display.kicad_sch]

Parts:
A1: RaspberryPi_Pico; RaspberryPi_Pico_Common_Unspecified
C1: 4700pf; C_Disc_D3.8mm_W2.6mm_P2.50mm
D1: LED; LED_D3.0mm
H1, H2, H3, H4: MountingHole_Pad; MountingHole_3.2mm_M3_DIN965
J1, J2: Conn_01x03_Pin; PinHeader_1x03_P2.54mm_Vertical
J3: Conn_01x02_Socket; JST_PH_B2B-PH-K_1x02_P2.00mm_Vertical
Q1, Q2, Q3, Q4, Q5, Q6: BS170; TO-92_Inline
R1: 120 ohm; R_Axial_DIN0204_L3.6mm_D1.6mm_P5.08mm_Vertical
R2, R3, R4, R5, R6, R7, R8, R9, R10, R11, R12, R13: 2.2 kΩ; R_Axial_DIN0204_L3.6mm_D1.6mm_P5.08mm_Vertical
R14: 100; R_Axial_DIN0204_L3.6mm_D1.6mm_P5.08mm_Vertical
U2: MCP2561-H-P; DIP-8_W7.62mm

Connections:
3.3VDC: A1.36 (3V3), Q1.2 (G), Q2.2 (G), Q3.2 (G), Q4.2 (G), Q5.2 (G), Q6.2 (G), R2.1, R4.1, R6.1, R8.1, R9.1, R10.1
FIS_CAN_ RXCAN: A1.16 (GPIO12), U2.4 (RXD)
FIS_CAN_TXCAN: A1.15 (GPIO11), U2.1 (TXD)
FIS_PIN_CLK: A1.2 (GPIO1), Q5.3 (S), R9.2
FIS_PIN_CLK_OUT: A1.6 (GPIO4), Q2.3 (S), R4.2
FIS_PIN_DATA: A1.4 (GPIO2), Q6.3 (S), R10.2
FIS_PIN_DATA_OUT: A1.7 (GPIO5), Q3.3 (S), R6.2
FIS_PIN_ENA: A1.1 (GPIO0), Q4.3 (S), R8.2
FIS_PIN_ENA_OUT: A1.5 (GPIO3), Q1.3 (S), R2.2
GND: A1.3 (GND), A1.8 (GND), A1.13 (GND), A1.18 (GND), A1.23 (GND), A1.28 (GND), A1.33 (AGND), A1.38 (GND), C1.2, H1.1, H2.1, H3.1, H4.1, R14.2, U2.2 (VSS), U2.8 (STBY)
unnamed: D1.1 (K), R14.1
unnamed: J3.1, R1.1, U2.7 (CANH)
unnamed: J3.2, R1.2, U2.6 (CANL)
unnamed: C1.1, U2.5 (SPLIT)
RX_CLK: J2.2, Q5.1 (D), R12.2
RX_DATA: J2.3, Q6.1 (D), R13.2
RX_ENA: J2.1, Q4.1 (D), R11.2
TX_CLK: J1.2, Q2.1 (D), R5.2
TX_DATA: J1.3, Q3.1 (D), R7.2
TX_ENA: J1.1, Q1.1 (D), R3.2
VDD: A1.40 (VBUS), D1.2 (A), R3.1, R5.1, R7.1, R11.1, R12.1, R13.1, U2.3 (VDD)

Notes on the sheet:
3LB RX
Bi-directional level shifters
FIS-Display Middleman
3LB TX

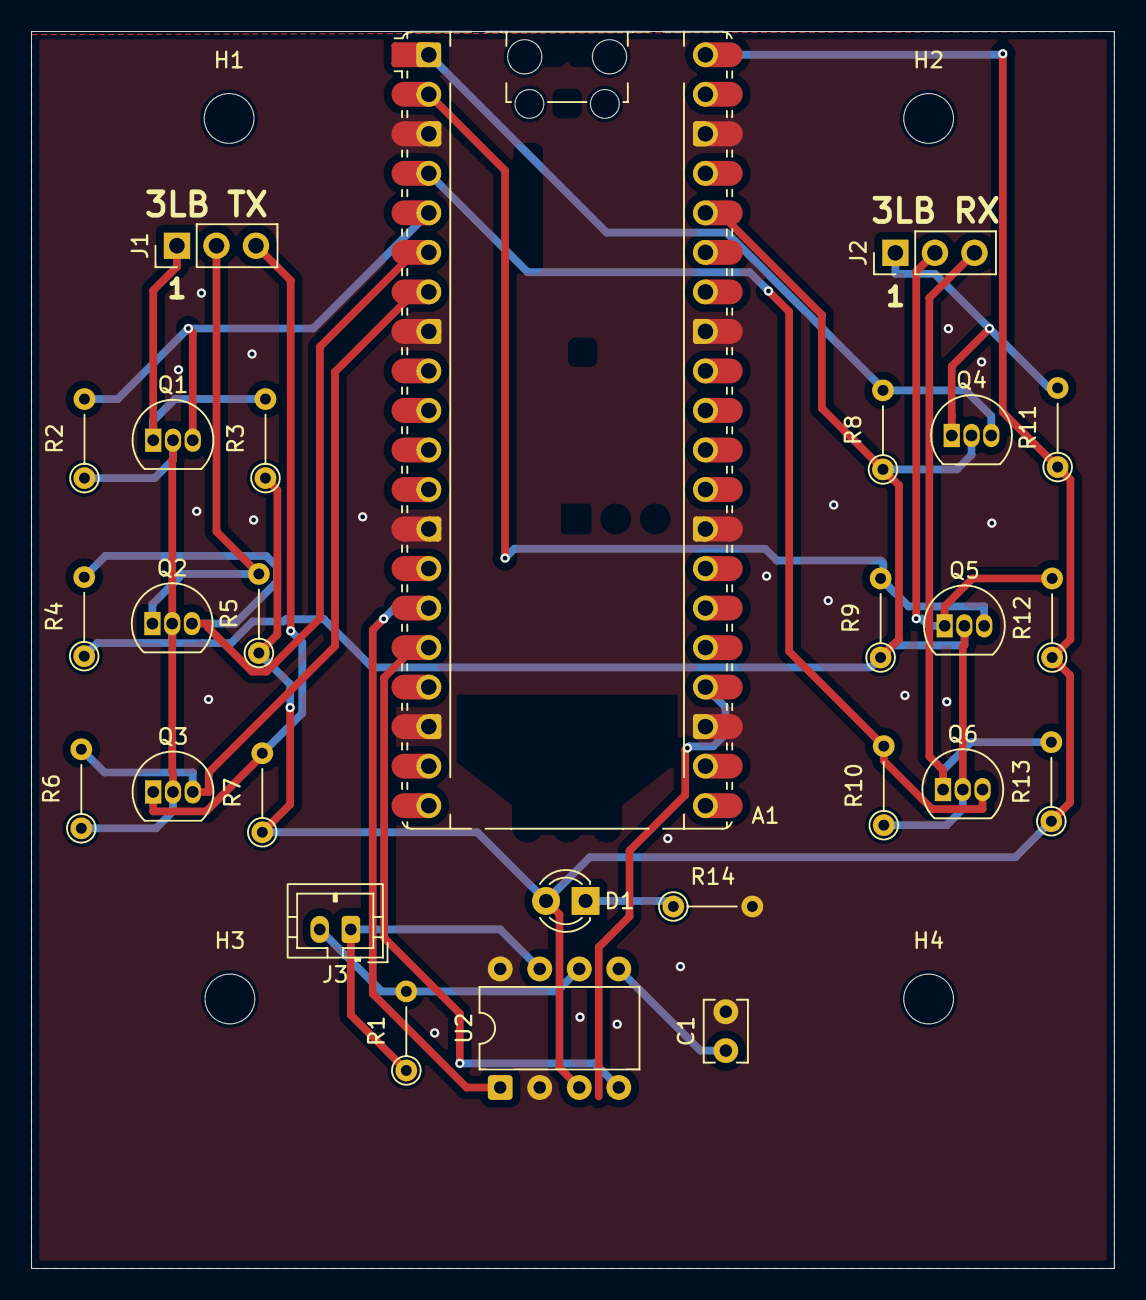
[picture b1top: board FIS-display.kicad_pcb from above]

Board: 2 copper layers, 69.6 x 79.5 mm, 31 parts (0 on the bottom side), 21 nets.

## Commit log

2026-03-12 Add Pico 2 W FIS bridge firmware and BOM
    Made-with: Cursor
2026-03-12 Add FIS firmware attribution and BOM fix
    Made-with: Cursor
2026-03-12 Document firmware experimental status
    Made-with: Cursor
2026-03-12 Firmware: align with README, drop HC-05; doc Bluetooth SPP as integrated
    Made-with: Cursor
2026-03-13 Tweak level shifter resistors and RX reset
    Made-with: Cursor
2026-03-13 Update README.md
    Added speed.
2026-03-14 Firmware: local time, ETA, compass, remain, feature toggles; docs and OEM CAN reference
    - Timezone from GPS: bbox table in flash, DST algorithm, UTC to local for clock and ETA
    - position_direction (NAV:HEAD) as compass on clock line 2; destination_length (NAV:REMAIN) on clock line 2
    - ETA (NAV:ETA) shown in local time as ARR HH:MM on clock line 2
    - Feature toggles: CFG:CLOCK, CFG:ETA, CFG:COMPASS, CFG:REMAIN (serial); fis_config_t, default all on
    - README: experimental note, PCB note, runtime/clock injection, CFG table, OEM CAN (mDiagnose_1, mEinheiten, mKombi_1/2/3, mGate_Komf_1, mZAS_1, mClima_1, Parkhilfe_01, mSysteminfo_1) reference tables
    - BOM: 2.2k resistor DigiKey P/N corrected to CF
2026-03-14 README: add table of contents with clickable anchor links
    Made-with: Cursor
2026-03-14 Add project structure, flashing docs, display test, nav icons, glossary
    - README: project structure section with all folders/docs linked (no symlinks)
    - firmware/README: Windows and macOS flashing instructions; Linux flash steps
    - firmware-display-test: standalone display test firmware and README with flash refs
    - firmware: 3LB graphics (0x53/0x55), nav icons, maneuver-to-icon mapping in bridge
    - nav-icons: SVG sources for fis_nav_icons bitmaps
    - PQ35 CAN matrix xlsx and DE-EN glossary
2026-03-14 Add icon tooling and docs: SVG converter, nav-icons README, Inkscape link
    - tools/svg_to_fis_icon.py: convert SVG to 64x64 1-bit C array (cairosvg/rsvg/ImageMagick + Pillow)
    - nav-icons/README.md: how to add icons, format, no-background rule, Inkscape link
    - README/firmware README: project structure links to tools and nav-icons; add custom icons steps
    - fis_nav_icons.h: self-doc format and add-icon steps
    - fis_display.c: comment bitmap/icon layout and inject behaviour
    Made-with: Cursor
2026-03-14 README: add CAN K-Matrix and Glossary links to Key References
    Made-with: Cursor
2026-03-14 Add toggleable CAN support (default off), config defaults, CAN hardware notes
    - CAN disabled by default in fis_config_defaults.h (FIS_CAN_ENABLED_DEFAULT 0)
    - CFG:CAN:0/1 serial toggle; fis_can stub for future MCP2515+MCP2551
    - Docs: B6 comfort CAN 100 kbit/s, MCP2551-I/P DIP-8, 8 MHz crystal, 22pF, 120 ohm, decoupling; 3.3V logic compatible, no level shifter
    Made-with: Cursor
2026-03-14 Docs: add optional CAN to system diagram, document CAN/SPI pins (GPIO10-13)
    - System overview diagram: Pico optional branch to MCP2515/MCP2551, comfort CAN 100 kbit/s
    - fis_can.h: define FIS_CAN_PIN_SCK/MOSI/MISO/CS (GPIO10-13) for SPI to MCP2515
    - README and firmware/README: optional CAN pinout table and Pico-MCP2515-MCP2551 wiring
    Made-with: Cursor
2026-03-14 Docs: CAN termination rules and non-inductive resistors
    - CAN termination: tapped middle (none), replacing radio (may need 120 ohm), bench (both ends); measure CAN-H to CAN-L ~60 ohm / ~120 ohm
    - Specify non-inductive resistors throughout (3LB pull-ups, damping, LED, CAN 120 ohm); metal film or SMD thick/thin film, avoid wirewound
    Made-with: Cursor
2026-03-14 README: KiCad PCB/schematic note, disclaimer; BOM and firmware updates
    - Note PCB and schematic designed in KiCad; link to pcb-files and Gerber section
    - Disclaimer: creator not responsible for damages, immobile car, injury, etc.
    - BOM: MCP2561, manufacturer P/Ns, qty fixes vs PCB CSV; remove polyfuse, 1k LED R, pushbutton
    - Firmware: CAN default off, MCP2561 GPIO 11/12 (TXD/RXD), config defaults
    - firmware README: CAN pinout, optional CAN description
    Made-with: Cursor
2026-03-14 Add datasheets and pcb-files (KiCad project, Gerbers, BOM CSV)
    Made-with: Cursor
2026-03-14 README: add Made with KiCad link (kicad.org)
    Made-with: Cursor
2026-03-14 README: reorganize - disclaimer first, what it does, Gerbers, then technical sections
    Made-with: Cursor
2026-03-14 README: explain Navit with link, correct description, list features (media, call, clock, ETA, compass, FIS-Bridge, display-test)
    Made-with: Cursor
2026-03-15 Full CAN support, OEM messages, SDK install, display-test build fix
    - firmware: software CAN 2.0A at 100 kbit/s (fis_can.c), GPIO 11/12, MCP2561
    - OEM Komfort-CAN: mDiagnose_1 (0x7D0) and mEinheiten (0x60E) sent every 1 s when CAN enabled
    - local_time_get_local_components() for GPS-to-local time; fis_can_oem_tick() in main loop
    - PIO fix: wait pin,0 syntax in fis_3lb_rx.pio; PIO_FDEBUG_TXOVER_LSB; critical_section.h; tz_lookup stddef.h
    - pico_sdk_import.cmake in firmware/ for SDK discovery; README SDK install instructions
    - README: Komfort-CAN vs ACAN/ICAN, J533 gateway; full CAN support wording
2026-03-15 gitignore: firmware-display-test build2/
    Made-with: Cursor
2026-03-15 BOM: replace PCB connectors with Molex kit; icons: regenerate data, add validation and regen script
    - Remove JST PH PCB headers and housings from BOM; add Molex 0766500064 kit (DigiKey 23-0766500064-ND) for pigtail or wire-to-wire 3LB connection
    - Doc: section 5.5 and firmware README describe RX/TX pigtail wiring (female 0003061038, plug 0003062033) and wire-to-wire use
    - Regenerate all 38 nav icon arrays in fis_nav_icons.h from SVGs; add all-zero check in svg_to_fis_icon.py and regenerate_nav_icons.py; document in nav-icons README and fis_nav_icons.h
    Made-with: Cursor
2026-03-15 PCB: update KiCad design and Gerbers; add design backups
    Made-with: Cursor
2026-03-15 BOM: remove optional TVS and debug header; renumber items 1-12; clarify 100R for LED
    Made-with: Cursor
2026-03-16 Eco mode icon: add SVG, FIS table, mapping; doc driver-break D-Bus and no-override policy
    - Add nav_eco-mode.svg and ICON_NAV_ECO_MODE to fis_nav_icons.h (FIS_ICON_COUNT 39)
    - Map NAV:TURN:eco_mode/eco to icon 38 in fis_display.c (driver-break plugin)
    - README 3.1: when to show eco (D-Bus eco-mode engaged, ECU, energy routing), must NOT override routing; how to add D-Bus attribute/signal and bridge logic (brief display then real maneuver)
    - nav-icons README: 39 icons, nav_eco_mode for driver-break eco mode
    - Key references: link to driver-break plugin docs
    Made-with: Cursor
2026-03-16 Add navit_dbus_to_pico_bridge.py with eco_mode_fuel_enabled support
    - Host script forwards Navit D-Bus to Pico over serial (USB/Bluetooth)
    - When eco_mode_fuel_enabled is true and route is ready, shows eco icon briefly then real first turn
    - README: document script, run instructions, and tools table entry
    Made-with: Cursor
2026-03-16 CAN RX parsing, README section 10: MSP3222 pinout and screen upgrade docs
    Firmware:
    - Add fis_can_rx: full K-CAN parsing (mKombi_1/2/3, mGate_Komf_1, mZAS_1, Parkhilfe_01)
    - fis_can_ensure_init(), integrate fis_can_rx_poll in bridge
    - Parsed state: speed, fuel, temp, brightness, ignition, doors, PDC, warnings, standzeit
    README section 10:
    - No firmware support for TFT/icons; use nav-icons for icon sources
2026-03-16 README: add PCB 3D image; update PCB/KiCad and Gerbers
    Made-with: Cursor
2026-03-17 README: section 10 formatting, LCD wiki/driver refs, ILI9341 window addressing; PCB/KiCad/PDF/Gerbers
    Made-with: Cursor
2026-03-17 3LB TX at ~125 kHz; README bus speed and arbitration; firmware note
    - fis_display.c: PIO clock divider for 3LB TX at FIS_3LB_TX_CLK_HZ (125000);
    add FIS_3LB_TX_CYCLES_PER_BIT, comment references README 5.2
    - README: 3LB speed suspected ~125-130 kHz, doc hard to find; add instructions
    to measure CLK and adjust FIS_3LB_TX_CLK_HZ; fix bus arbitration (pull ENA
    low to claim, wait when ENA low)
    - firmware/README: note on TX clock ~125 kHz and link to main README 5.2
